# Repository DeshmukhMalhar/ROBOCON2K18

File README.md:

# ROBOCON2K18

repo for all the technical data generated by us for robocon 2018

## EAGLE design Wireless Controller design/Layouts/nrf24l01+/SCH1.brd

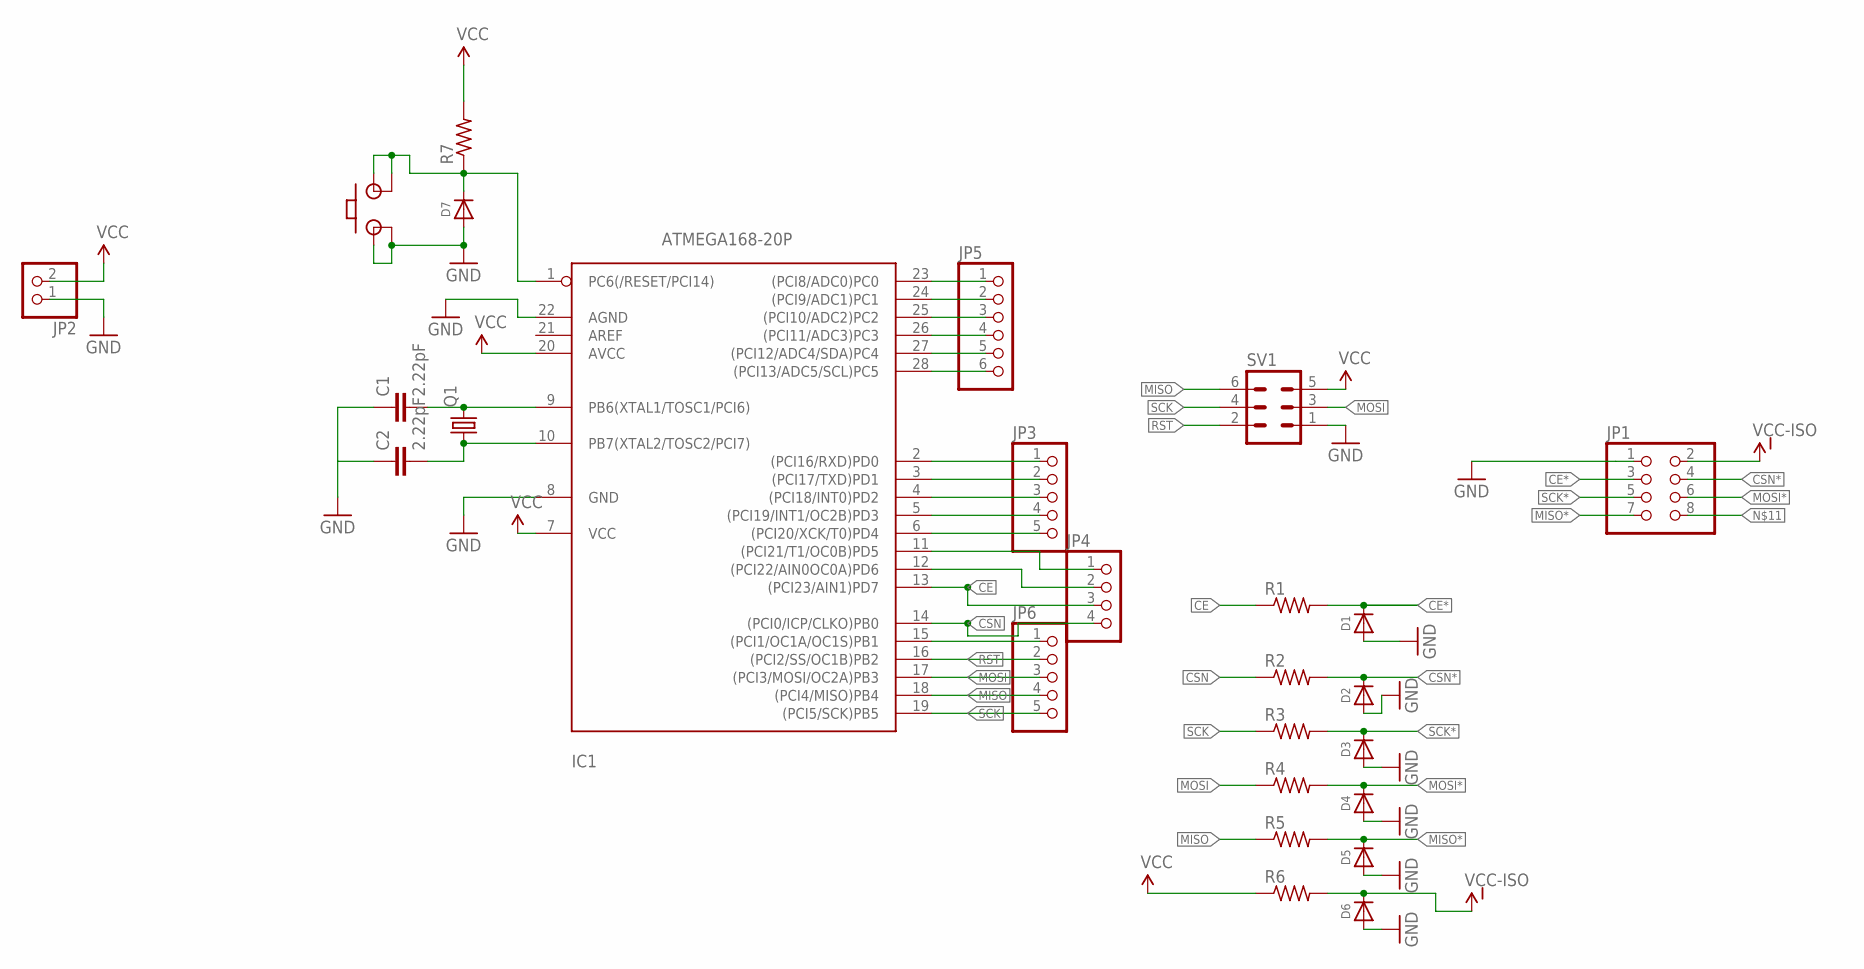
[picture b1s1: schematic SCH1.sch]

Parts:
C1, C2: 2.22pF; C025-024X044
D1, D2, D3, D4, D5, D6, D7: DIODEDO-1N4148; DO-1N4148
IC1: ATMEGA168-20P; DIL28-3
JP1: PINHD-2X4; 2X04
JP2: PINHD-1X2; 1X02
JP3, JP6: PINHD-1X5; 1X05
JP4: PINHD-1X4; 1X04
JP5: PINHD-1X6; 1X06
PB1: TACTSW
Q1: CRYSTALHC49U-V; HC49U-V
R1, R2, R3, R4, R5, R6, R7: R-US_0207/7; 0207/7
SV1: MA03-2

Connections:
CE: IC1.13 ((PCI23/AIN1)PD7), JP4.3, R1.1
CE*: D1.C, JP1.3, R1.2
CSN: IC1.14 ((PCI0/ICP/CLKO)PB0), JP4.4, R2.1
CSN*: D2.C, JP1.4, R2.2
GND: C1.1, C2.1, D1.A, D2.A, D3.A, D4.A, D5.A, D6.A, D7.A, IC1.8 (GND), IC1.22 (AGND), JP1.1, JP2.1, PB1.P$1, PB1.P$2, SV1.1
MISO: IC1.18 ((PCI4/MISO)PB4), JP6.4, R5.1, SV1.6
MISO*: D5.C, JP1.7, R5.2
MOSI: IC1.17 ((PCI3/MOSI/OC2A)PB3), JP6.3, R4.1, SV1.3
MOSI*: D4.C, JP1.6, R4.2
unnamed: C1.2, IC1.9 (PB6(XTAL1/TOSC1/PCI6)), Q1.2
unnamed: C2.2, IC1.10 (PB7(XTAL2/TOSC2/PCI7)), Q1.1
unnamed: D7.C, IC1.1 (PC6(/RESET/PCI14)), PB1.P$3, PB1.P$4, R7.1
unnamed: IC1.2 ((PCI16/RXD)PD0), JP3.1
unnamed: IC1.3 ((PCI17/TXD)PD1), JP3.2
unnamed: IC1.4 ((PCI18/INT0)PD2), JP3.3
unnamed: IC1.5 ((PCI19/INT1/OC2B)PD3), JP3.4
unnamed: IC1.6 ((PCI20/XCK/T0)PD4), JP3.5
unnamed: IC1.11 ((PCI21/T1/OC0B)PD5), JP4.1
unnamed: IC1.12 ((PCI22/AIN0OC0A)PD6), JP4.2
unnamed: IC1.23 ((PCI8/ADC0)PC0), JP5.1
unnamed: IC1.24 ((PCI9/ADC1)PC1), JP5.2
unnamed: IC1.25 ((PCI10/ADC2)PC2), JP5.3
unnamed: IC1.26 ((PCI11/ADC3)PC3), JP5.4
unnamed: IC1.27 ((PCI12/ADC4/SDA)PC4), JP5.5
unnamed: IC1.28 ((PCI13/ADC5/SCL)PC5), JP5.6
unnamed: IC1.15 ((PCI1/OC1A/OC1S)PB1), JP6.1
RST: IC1.16 ((PCI2/SS/OC1B)PB2), JP6.2, SV1.2
SCK: IC1.19 ((PCI5/SCK)PB5), JP6.5, R3.1, SV1.4
SCK*: D3.C, JP1.5, R3.2
VCC: IC1.7 (VCC), IC1.20 (AVCC), JP2.2, R6.1, R7.2, SV1.5
VCC-ISO: D6.C, JP1.2, R6.2

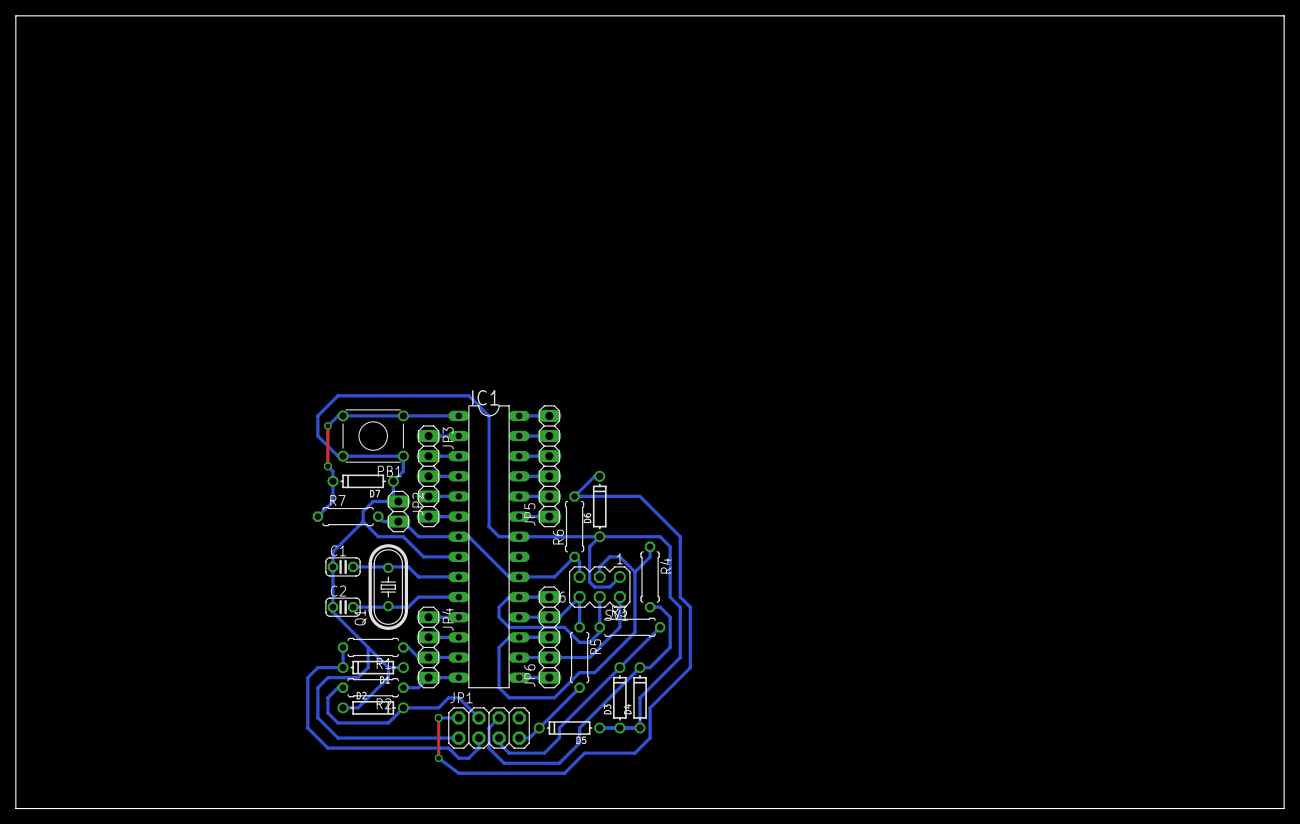
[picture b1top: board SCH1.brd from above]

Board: 2 copper layers, 160.0 x 100.0 mm, 26 parts (0 on the bottom side), 31 nets.

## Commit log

2017-12-18 moved files into folder
2017-12-29 Aded codes for testing new motor
2017-12-30 Reorganised the folder stracture
2017-12-30 Added PCB files for MOSFET DRIVER
2018-01-08 created repo for cytron codes
2018-01-09 added both codes primitive and optimized
2018-01-11 added folder stracture for new wireless controller
2018-01-14 schematics and board layout added.
    aeKUTuvug55
2018-01-14 Added basic sketch for closed loop controller
2018-01-14 Added the PCB layout for PID controller
2018-01-15 Modified the PID controller sketch for new Board
2018-01-16 Changed Tuning Parameters in PID controller
2018-01-19 Added new Cytron code
2018-01-20 Added I2C recv to PID controller. Added libraries
2018-01-20 Organized omni_cytron_test folder
2018-01-20 Removed serial prints
2018-01-20 Optimized
2018-01-21 Optimised
2018-01-21 Added description for code in Closed LOOP Motor Driver
2018-01-21 Added a critical assignment in PID controller sketch
2018-01-21 Added 8 digit display to repo
2018-01-23 Added 'I2c_anything' modified sketches
2018-01-24 Added library for Motor driver
2018-01-27 created folder Magnetometer and added code
2018-01-30 added code for cytron T config along with magnetometer
2018-01-30 Small changes and added gitignore
2018-02-01 made some minor changes
2018-02-02 some changes
2018-02-02 testing
2018-02-06 Final Code
2018-02-07 added motordriver library
2018-02-08 Changed a wrong fuse setting in AVRDUDE commands
2018-02-08 Modified IIC devlopement sketches in closed loop driver
2018-02-10 New updated code
2018-02-10 Optimised dynamic memory and time
2018-02-11 Started cleaning up arduino sketches
2018-02-12 changed pwm values for auto bot
2018-02-15 Added code for improved pinging
2018-02-15 enhanced code
2018-02-17 added code for proximity sensor
2018-02-18 enhanced traversal and added code for shuttlecock detection
2018-02-19 added Hardware definations for Wireless controller
2018-02-20 minor changes
2018-02-21 tuned for new bot
2018-02-23 added code for neopixel
2018-02-23 added code for pneumatic relay
2018-02-24 added code for daughter board
2018-02-25 added code for new motherboard and daughterboard
2018-02-25 code almost to be discarded communication 6 pins vaalaa
2018-02-25 almost final auto bot code
2018-02-27 minor additions
2018-02-27 just for self confirmation

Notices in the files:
parts and their libraries:
SparkFun-Aesthetics: Licensing: Creative Commons ShareAlike 4.0 International - https://creativecommons.org/licenses/by-sa/4.0
